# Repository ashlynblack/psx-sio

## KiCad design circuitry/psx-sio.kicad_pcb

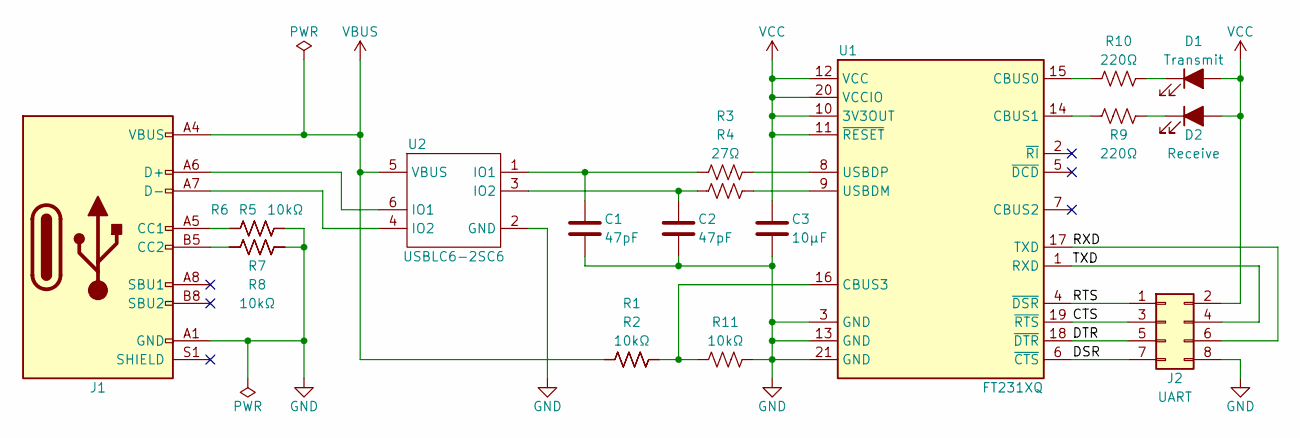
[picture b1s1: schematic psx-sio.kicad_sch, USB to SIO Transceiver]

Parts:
C1, C2: 47pF; C_0603_1608Metric
C3: 10µF; C_0603_1608Metric
D1, D2: LED_Filled; LED_1206_3216Metric
J1: USB_C_Receptacle_USB2.0_16P; USB_C_Receptacle_HCTL_HC-TYPE-C-16P-01A
J2: Conn_02x04_Odd_Even; PinHeader_2x04_P2.54mm_Horizontal
R1, R2, R5, R6, R7, R8, R11: 10kΩ; R_0603_1608Metric
R3, R4: 27Ω; R_0603_1608Metric
R9, R10: 220Ω; R_0603_1608Metric
U1: FT231XQ; QFN-20-1EP_4x4mm_P0.5mm_EP2.5x2.5mm
U2: USBLC6-2SC6; SOT-23-6

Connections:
/CTS: J2.3, U1.19 (~RTS)
/DSR: J2.7, U1.6 (~CTS)
/DTR: J2.5, U1.18 (~DTR)
/RTS: J2.1, U1.4 (~DSR)
/RXD: J2.6, U1.17 (TXD)
/TXD: J2.4, U1.1 (RXD)
GND: C1.2, C2.2, C3.2, J1.A1 (GND), J1.A12 (GND), J1.B1 (GND), J1.B12 (GND), J2.8, R5.2, R6.2, R7.2, R8.2, R11.1, U1.3 (GND), U1.13 (GND), U1.21 (GND), U2.2 (GND)
unnamed: C1.1, R3.1, U2.1 (IO1)
unnamed: C2.1, R4.1, U2.3 (IO2)
unnamed: D1.1 (K), R10.2
unnamed: D2.1 (K), R9.2
unnamed: J1.A5 (CC1), R5.1, R6.1
unnamed: J1.B5 (CC2), R7.1, R8.1
unnamed: J1.A6 (D+), J1.B6 (D+), U2.6 (IO1)
unnamed: J1.A7 (D-), J1.B7 (D-), U2.4 (IO2)
unnamed: R10.1, U1.15 (CBUS0)
unnamed: R9.1, U1.14 (CBUS1)
unnamed: R1.1, R2.1, R11.2, U1.16 (CBUS3)
unnamed: R4.2, U1.9 (USBDM)
unnamed: R3.2, U1.8 (USBDP)
VBUS: J1.A4 (VBUS), J1.A9 (VBUS), J1.B4 (VBUS), J1.B9 (VBUS), R1.2, R2.2, U2.5 (VBUS)
VCC: C3.1, D1.2 (A), D2.2 (A), J2.2, U1.10 (3V3OUT), U1.11 (~RESET), U1.12 (VCC), U1.20 (VCCIO)

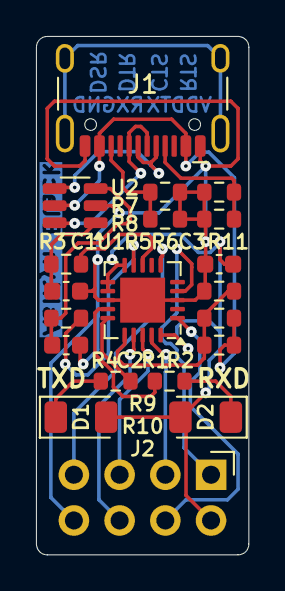
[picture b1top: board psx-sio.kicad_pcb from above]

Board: 2 copper layers, 11.8 x 28.8 mm, 20 parts (0 on the bottom side), 22 nets.

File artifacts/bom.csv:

"Reference","Value","Footprint","Qty"
"C1,C2","47pF","Capacitor_SMD:C_0603_1608Metric","2"
"C3","10µF","Capacitor_SMD:C_0603_1608Metric","1"
"D1,D2","LED_Filled","LED_SMD:LED_1206_3216Metric","2"
"J1","USB_C_Receptacle_USB2.0_16P","Connector_USB:USB_C_Receptacle_HCTL_HC-TYPE-C-16P-01A","1"
"R1,R2,R5,R6,R7,R8,R11","10kΩ","Resistor_SMD:R_0603_1608Metric","7"
"R3,R4","27Ω","Resistor_SMD:R_0603_1608Metric","2"
"R9,R10","220Ω","Resistor_SMD:R_0603_1608Metric","2"
"U1","FT231XQ","Package_DFN_QFN:QFN-20-1EP_4x4mm_P0.5mm_EP2.5x2.5mm","1"
"U2","USBLC6-2SC6","Package_TO_SOT_SMD:SOT-23-6","1"

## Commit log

2024-07-09 Tracked PDF, PNG and ZIP files with Git LFS.
2024-07-09 Ignored extraneous files.
2024-07-09 Added articles and datasheets to research.
2024-07-09 Schematic and layout completed.
2024-07-09 Ignored KiCAD backups.
2024-07-09 Added project artifacts.
2024-07-10 Generated interactive bill of materials.
2024-07-27 Changed schematic to black and white.
